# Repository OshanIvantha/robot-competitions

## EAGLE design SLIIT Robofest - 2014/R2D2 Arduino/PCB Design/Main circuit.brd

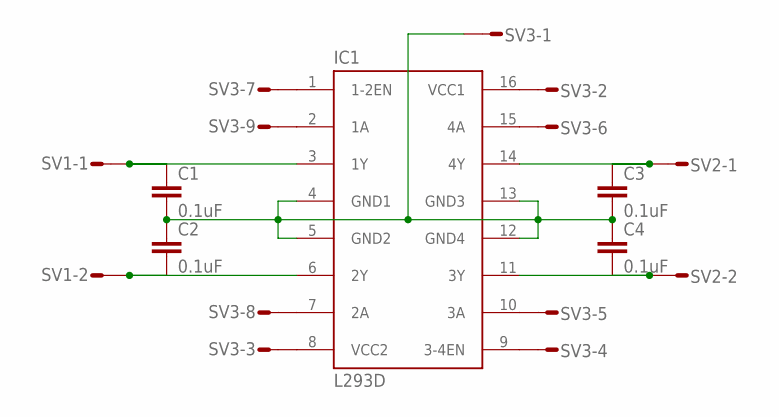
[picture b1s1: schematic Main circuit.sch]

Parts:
C1, C2, C3, C4: 0.1uF; C2.5-2
IC1: L293D; DIL16
SV1, SV2: L02P
SV3: L09P

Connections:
unnamed: C1.2, C2.1, C3.2, C4.1, IC1.4 (GND1), IC1.5 (GND2), IC1.12 (GND4), IC1.13 (GND3), SV3.1
unnamed: IC1.7 (2A), SV3.8
unnamed: IC1.2 (1A), SV3.9
unnamed: IC1.1 (1-2EN), SV3.7
unnamed: C1.1, IC1.3 (1Y), SV1.1
unnamed: C2.2, IC1.6 (2Y), SV1.2
unnamed: C4.2, IC1.11 (3Y), SV2.2
unnamed: C3.1, IC1.14 (4Y), SV2.1
unnamed: IC1.15 (4A), SV3.6
unnamed: IC1.10 (3A), SV3.5
unnamed: IC1.9 (3-4EN), SV3.4
unnamed: IC1.8 (VCC2), SV3.3
unnamed: IC1.16 (VCC1), SV3.2

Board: 2 copper layers, 8 parts (0 on the bottom side), 13 nets, no tracks yet.

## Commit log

2017-11-14 Repo init.
2018-11-24 [ImgBot] Optimize images
    *Total -- 102.43kb -> 39.62kb (61.32%)
    /IESL RoboGames - 2016/robogames_pi/sample/white.png -- 19.46kb -> 0.42kb (97.82%)
    /IESL RoboGames - 2016/robogames_pi/sample/black.png -- 19.47kb -> 0.43kb (97.81%)
    /SLIIT Robofest - 2016/robofest_pi/sample/arrows.png -- 8.68kb -> 1.64kb (81.09%)
    /SLIIT Robofest - 2016/robofest_pi/sample/red_arrow.png -- 25.29kb -> 9.33kb (63.09%)
    /SLIIT Robofest - 2016/robofest_pi/sample/red_cube.jpg -- 29.54kb -> 27.79kb (5.89%)
